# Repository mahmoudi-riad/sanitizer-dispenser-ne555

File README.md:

# Touchless Sanitizer Dispenser (No MCU)

Lately, during an internship, I built a sanitizer dispenser using only **electronic components** (no programming / no microcontroller), including an 
**NE555 timer** and an industrial **proximity sensor (NPN)**.  
The NE555 controls the timing, allowing the dispenser to release sanitizer for about **1 second** each time it detects a hand.  

This repository contains the **schematic and PCB files** for the project in Kicad, ready for assembly.

## Files
just download all the files and put them in a foulder and open it with kicad , you find there 
shymatics and pcb

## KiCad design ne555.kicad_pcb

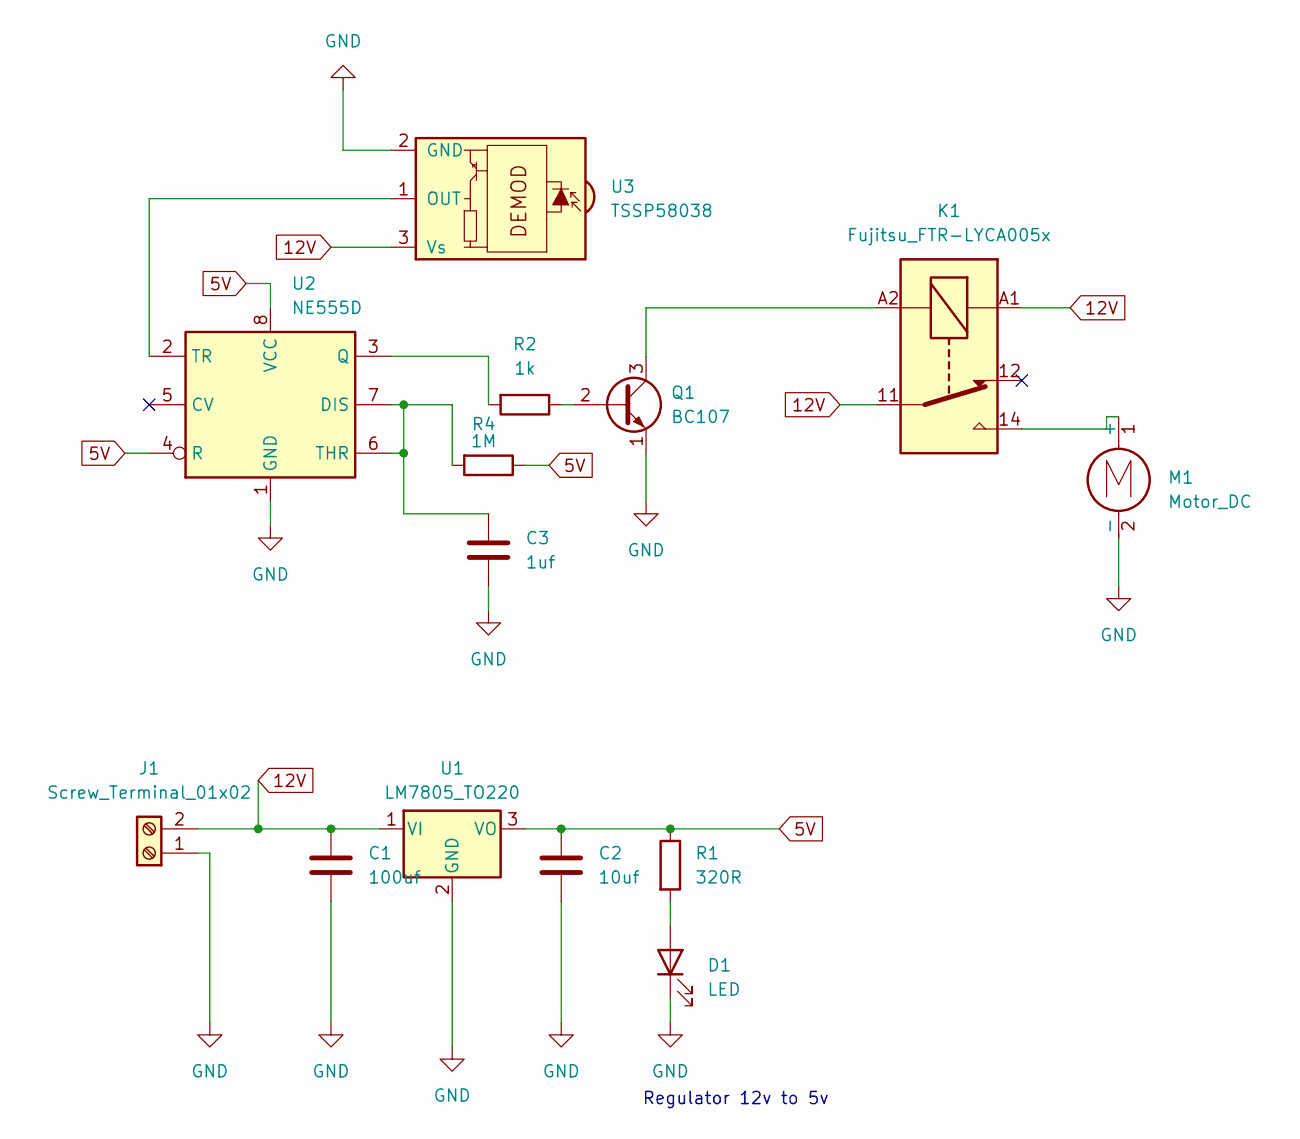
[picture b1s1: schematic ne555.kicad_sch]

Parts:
C1: 100uf; C_Radial_D6.3mm_H7.0mm_P2.50mm
C2: 10uf; C_Radial_D6.3mm_H7.0mm_P2.50mm
C3: 1uf; C_Radial_D6.3mm_H7.0mm_P2.50mm
D1: LED; LED_D8.0mm
J1: Screw_Terminal_01x02; TerminalBlock_Phoenix_MKDS-1,5-2_1x02_P5.00mm_Horizontal
K1: Fujitsu_FTR-LYCA005x; Relay_SPDT_Finder_36.11
M1: Motor_DC; L_Ferrocore_DLG-0504
Q1: BC107; TO-18-3
R1: 320R; R_Axial_DIN0204_L3.6mm_D1.6mm_P7.62mm_Horizontal
R2: 1k; R_Axial_DIN0204_L3.6mm_D1.6mm_P7.62mm_Horizontal
R4: 1M; R_Axial_DIN0204_L3.6mm_D1.6mm_P7.62mm_Horizontal
U1: LM7805_TO220; TO-220-3_Vertical
U2: NE555D; SOIC-8_3.9x4.9mm_P1.27mm
U3: TSSP58038; Vishay_MINICAST-3Pin

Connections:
5V: C2.1, R1.1, R4.1, U1.3 (VO), U2.4 (R), U2.8 (VCC)
12V: C1.1, J1.2, K1.11, K1.A1, U1.1 (VI), U3.3 (Vs)
GND: C1.2, C2.2, C3.2, D1.1 (K), J1.1, M1.2 (-), Q1.1 (E), U1.2 (GND), U2.1 (GND), U3.2 (GND)
unnamed: D1.2 (A), R1.2
unnamed: K1.14, M1.1 (+)
unnamed: Q1.2 (B), R2.1
unnamed: K1.A2, Q1.3 (C)
unnamed: C3.1, R4.2, U2.6 (THR), U2.7 (DIS)
unnamed: R2.2, U2.3 (Q)
unnamed: U2.2 (TR), U3.1 (OUT)

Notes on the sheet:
Regulator 12v to 5v

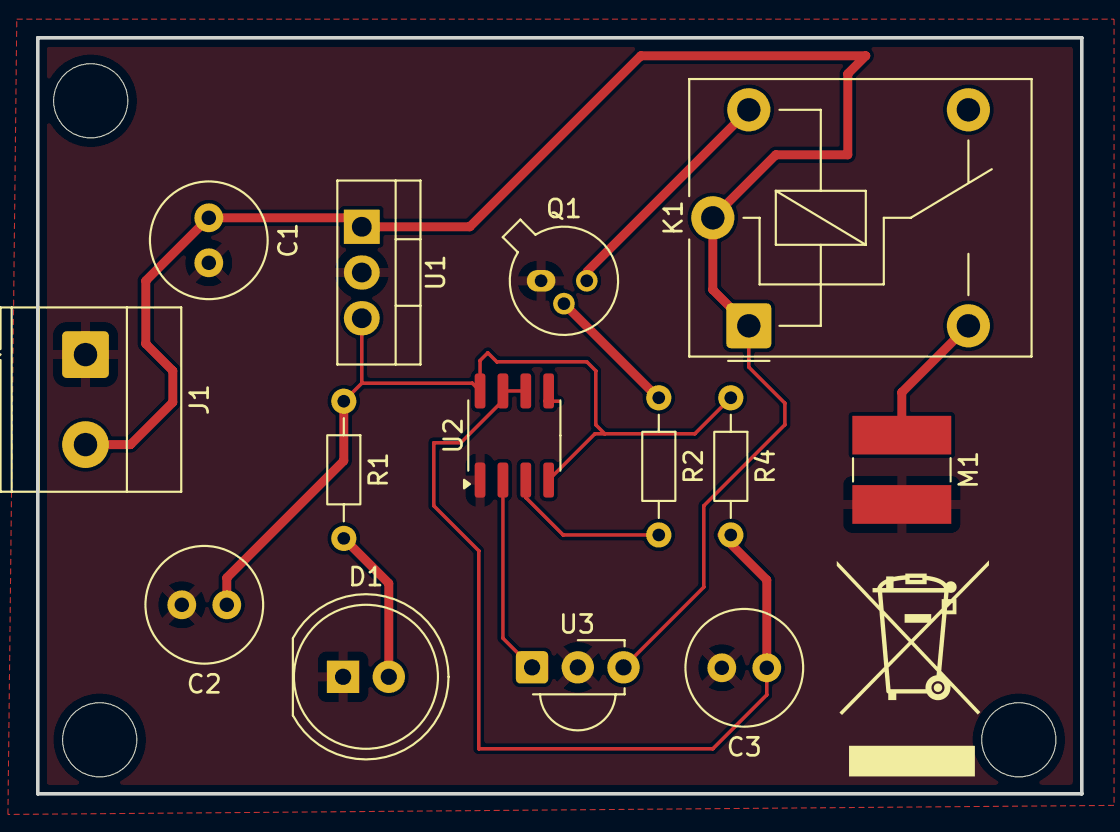
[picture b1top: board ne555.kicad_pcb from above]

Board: 2 copper layers, 58.0 x 42.0 mm, 14 parts (0 on the bottom side), 10 nets.
